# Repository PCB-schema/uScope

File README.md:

# uScope
Electron microscope
Project created with KiCAD v 5.0.2-bee76a0~70~ubuntu18.04.1, release build

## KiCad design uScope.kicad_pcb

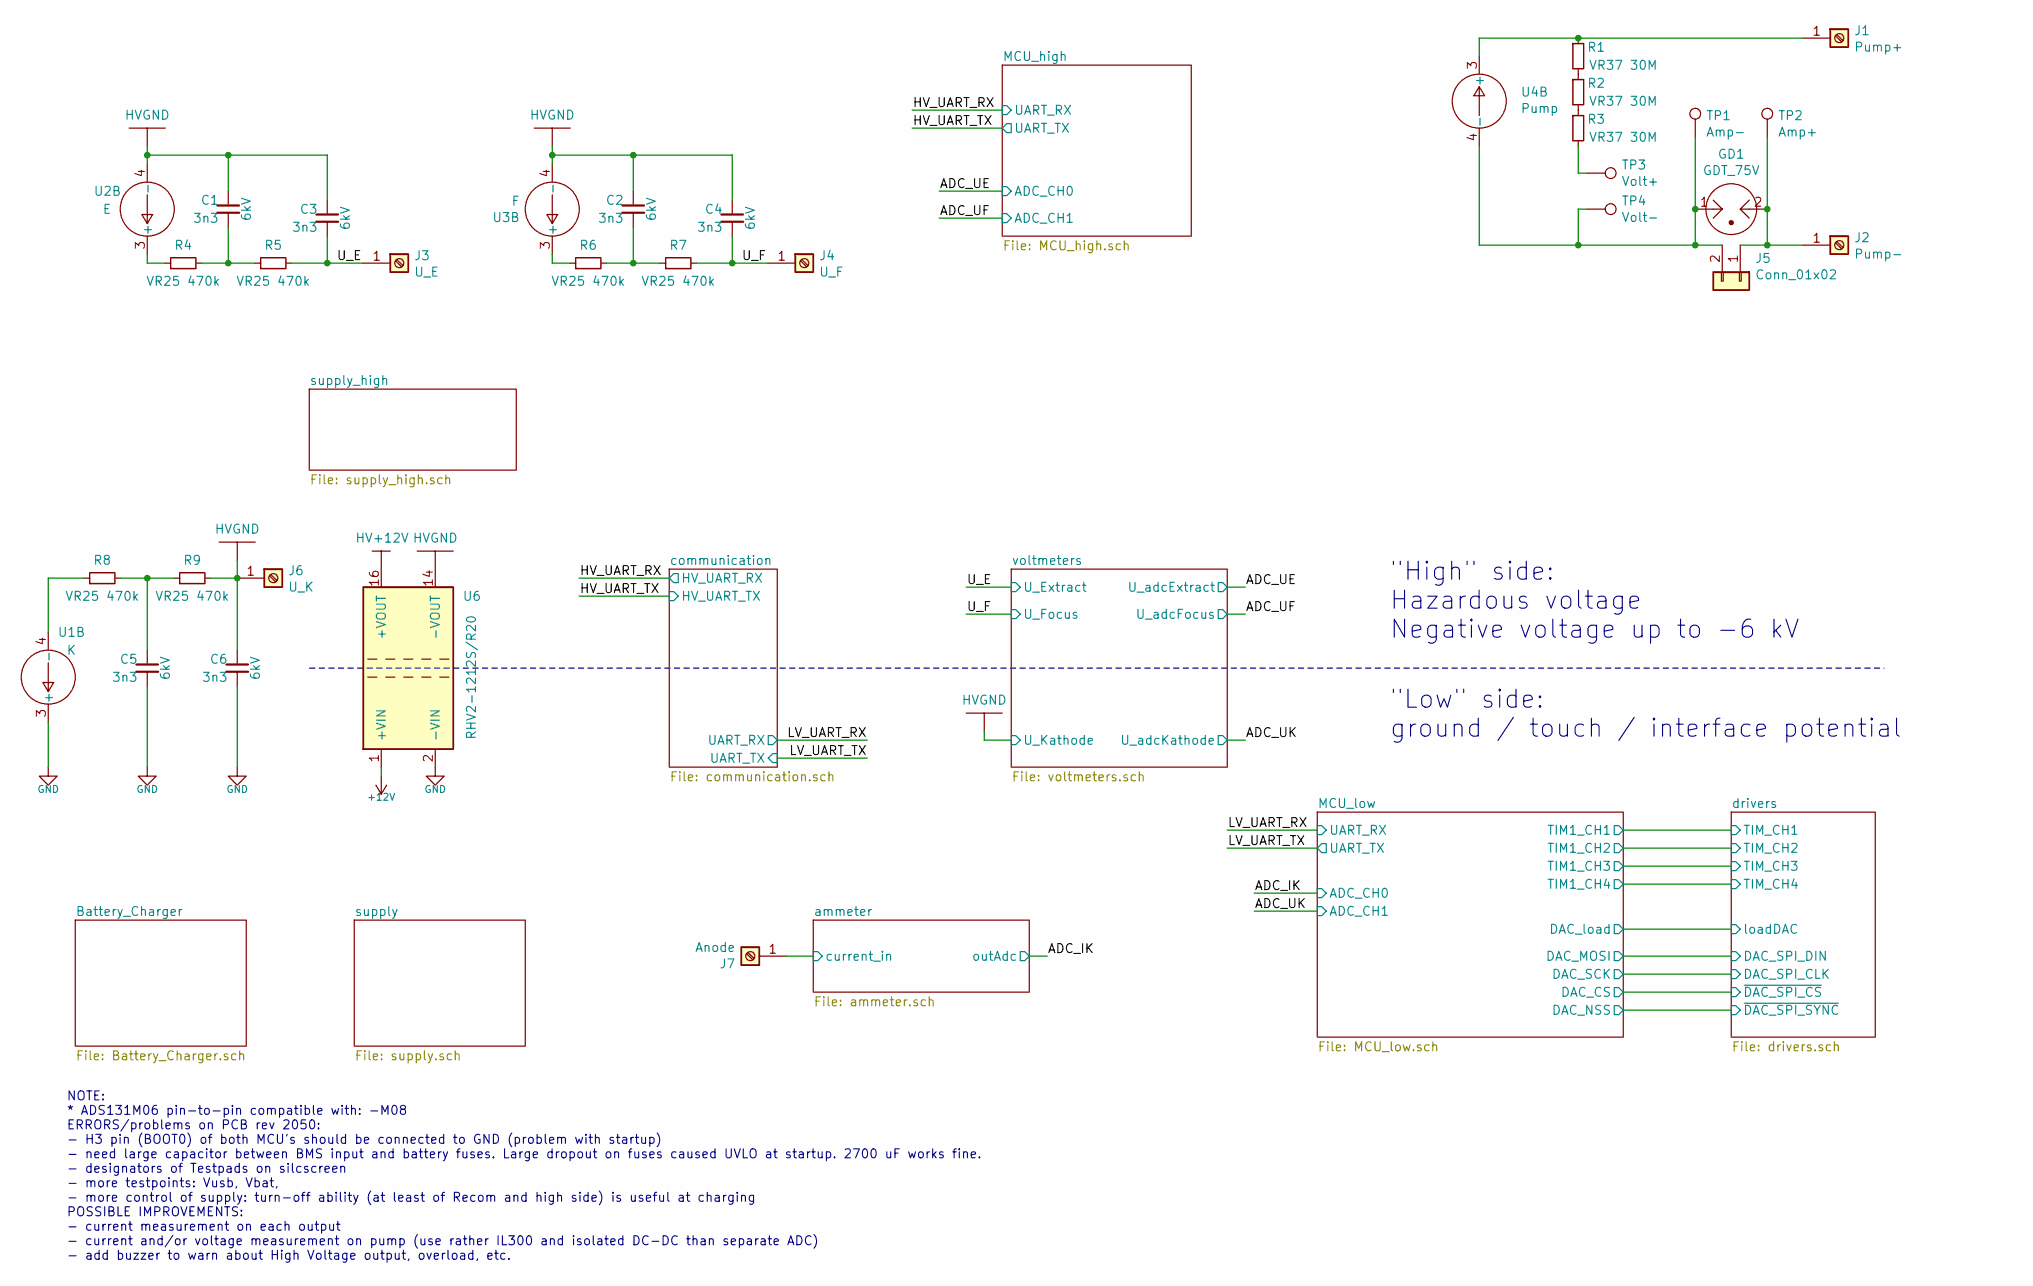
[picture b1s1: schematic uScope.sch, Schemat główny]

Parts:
C1, C2, C3, C4, C5, C6: 3n3; C_Rect_L26.5mm_W10.5mm_P22.50mm_MKS4; Voltage 6kV
GD1: GDT_75V; Arrester_Axial_L6mm_D6mm_P8.89mm_Horizontal
J1: Pump+; Terminal_Amp_HB0101
J2: Pump-; Terminal_Amp_HB0101
J3: U_E; Terminal_Amp_HB0101
J4: U_F; Terminal_Amp_HB0101
J5: Conn_01x02; PinHeader_1x02_P2.54mm_Vertical
J6: U_K; Terminal_Amp_HB0101
J7: Anode; Terminal_Amp_HB0101
R1, R2, R3: VR37 30M; R_Axial_DIN0411_L9.9mm_D3.6mm_P12.70mm_Horizontal
R4, R5, R6, R7, R8, R9: VR25 470k; R_Axial_DIN0207_L6.3mm_D2.5mm_P10.16mm_Horizontal
TP1: Amp-; Banana4mmSocket_black
TP2: Amp+; Banana4mmSocket_red
TP3: Volt+; Banana4mmSocket_red
TP4: Volt-; Banana4mmSocket_black
U1: K; DCDC_APD_P2_single
U2: E; DCDC_APD_P2_single
U3: F; DCDC_APD_P2_single
U4: Pump; DCDC_APD_P2_single
U6: RHV2-1212S/R20; SIP16_RECOM

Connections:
+12V: U6.1 (+VIN); also elsewhere on the board
/U_E: C3.2, J3.1, R5.2; also elsewhere on the board
/U_F: C4.2, J4.1, R7.2; also elsewhere on the board
/ammeter/current_in: J7.1; also elsewhere on the board
HV+12V: U6.16 (+VOUT); also elsewhere on the board
unnamed: C1.2, R4.2, R5.1
unnamed: C2.2, R6.2, R7.1
unnamed: C5.1, R8.2, R9.1
unnamed: GD1.1, J5.2, TP1.1, TP4.1, U4.4 (-)
unnamed: GD1.2, J2.1, J5.1, TP2.1
unnamed: J1.1, R1.1, U4.3 (+)
unnamed: R1.2, R2.1
unnamed: R2.2, R3.1
unnamed: R3.2, TP3.1
unnamed: R4.1, U2.3 (+)
unnamed: R6.1, U3.3 (+)
unnamed: R8.1, U1.4 (-)

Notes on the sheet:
NOTE: * ADS131M06 pin-to-pin compatible with: -M08 ERRORS/problems on PCB rev 2050: - H3 pin (BOOT0) of both MCU's should be connected to GND (problem with startup) - need large capacitor between BMS input and battery fuses. Large dropout on fuses caused UVLO at startup. 2700 uF works fine. - desig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
"High" side: Hazardous voltage Negative voltage up to -6 kV
"Low" side: ground / touch / interface potential

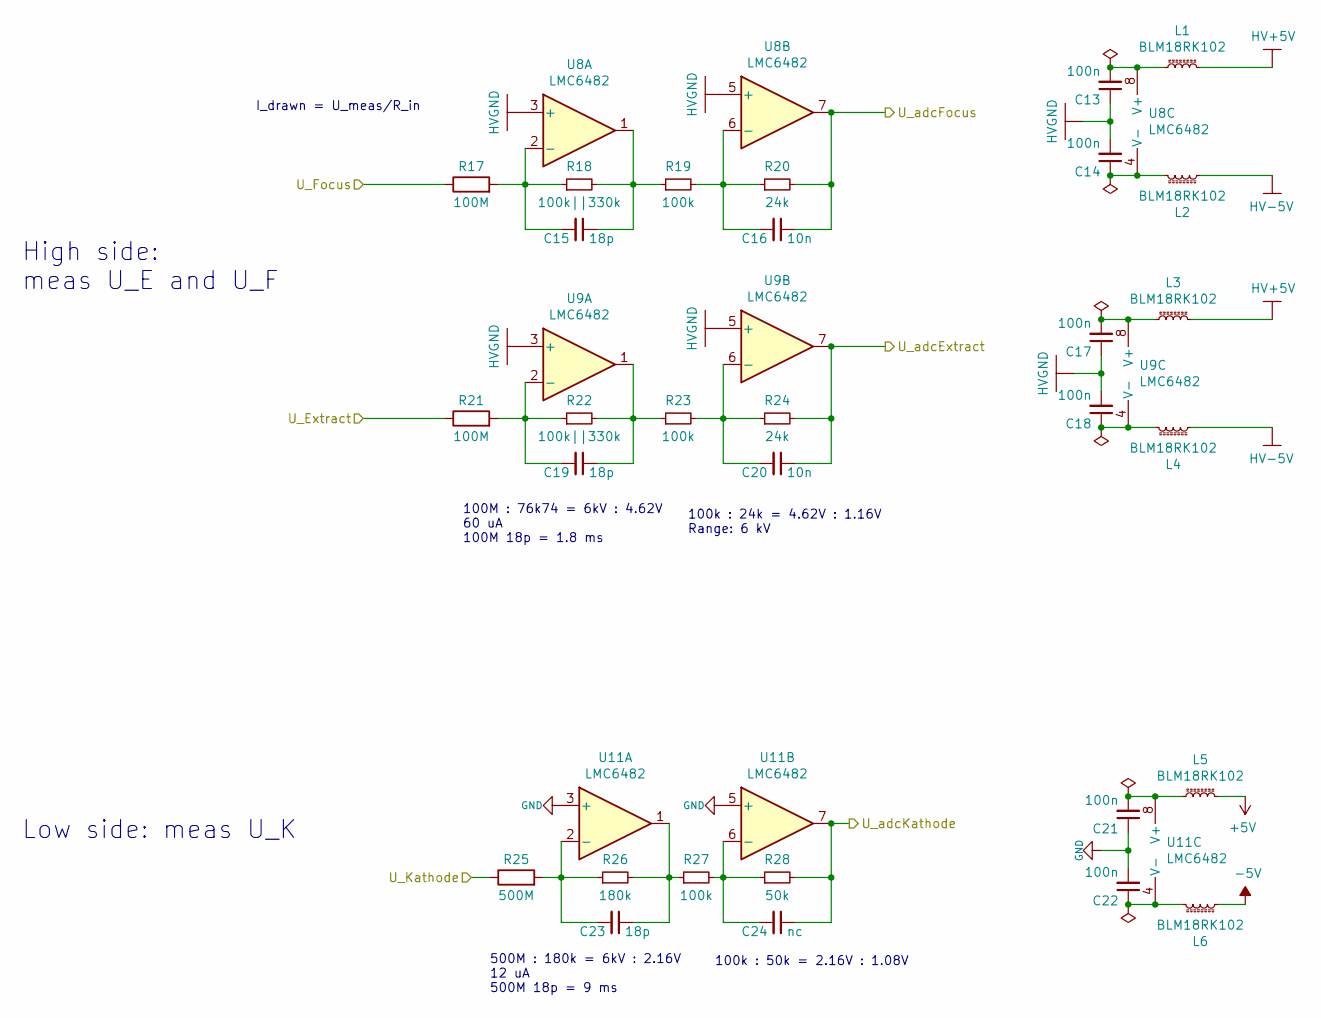
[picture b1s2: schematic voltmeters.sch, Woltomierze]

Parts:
C13, C14, C17, C18, C21, C22: 100n; C_0603_1608Metric
C15, C19, C23: 18p; C_0603_1608Metric
C16, C20: 10n; C_0603_1608Metric
C24: nc; C_0603_1608Metric
L1, L2, L3, L4, L5, L6: BLM18RK102; L_0603_1608Metric
R17, R21: 100M; MHR0317_0422_0424_0624SA
R18, R22: 100k||330k; R_0603_1608Metric
R19, R23, R27: 100k; R_0603_1608Metric
R20, R24: 24k; R_0603_1608Metric
R25: 500M; MHR0317_0422_0424_0624SA
R26: 180k; R_0603_1608Metric
R28: 50k; R_0603_1608Metric
U8, U9, U11: LMC6482; SO8-MSOP8_3x3mm_P0.65mm

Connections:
+5V: L5.2; also elsewhere on the board
-5V: L6.1; also elsewhere on the board
/ADC_UE: C20.1, R24.2, U9.7; also elsewhere on the board
/ADC_UF: C16.1, R20.2, U8.7; also elsewhere on the board
/ADC_UK: C24.1, R28.2, U11.7; also elsewhere on the board
/U_E: R21.1; also elsewhere on the board
/U_F: R17.1; also elsewhere on the board
HV+5V: L1.2, L3.2; also elsewhere on the board
HV-5V: L2.1, L4.1; also elsewhere on the board
unnamed: C13.2, L1.1, U8.8 (V+)
unnamed: C14.1, L2.2, U8.4 (V-)
unnamed: C15.1, R18.2, R19.1, U8.1
unnamed: C15.2, R17.2, R18.1, U8.2 (-)
unnamed: C16.2, R19.2, R20.1, U8.6 (-)
unnamed: C17.2, L3.1, U9.8 (V+)
unnamed: C18.1, L4.2, U9.4 (V-)
unnamed: C19.1, R22.2, R23.1, U9.1
unnamed: C19.2, R21.2, R22.1, U9.2 (-)
unnamed: C20.2, R23.2, R24.1, U9.6 (-)
unnamed: C21.2, L5.1, U11.8 (V+)
unnamed: C22.1, L6.2, U11.4 (V-)
unnamed: C23.1, R26.2, R27.1, U11.1
unnamed: C23.2, R25.2, R26.1, U11.2 (-)
unnamed: C24.2, R27.2, R28.1, U11.6 (-)

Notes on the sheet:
I_drawn = U_meas/R_in
Low side: meas U_K
High side: meas U_E and U_F
500M : 180k = 6kV : 2.16V 12 uA 500M 18p = 9 ms
100k : 50k = 2.16V : 1.08V
100M : 76k74 = 6kV : 4.62V 60 uA 100M 18p = 1.8 ms
100k : 24k = 4.62V : 1.16V Range: 6 kV

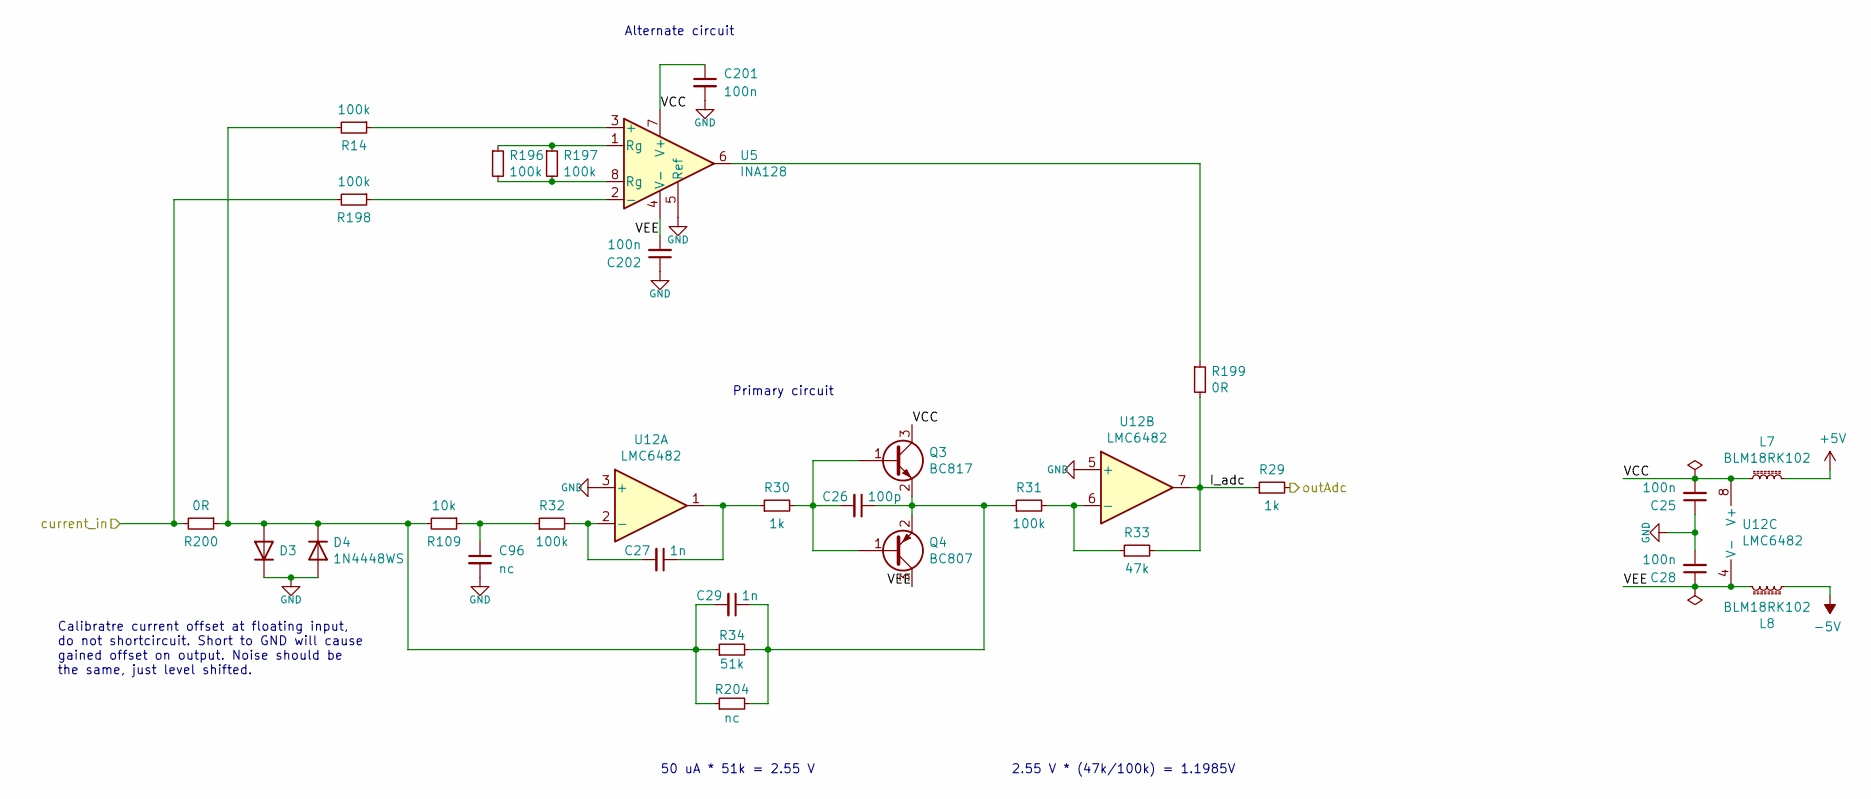
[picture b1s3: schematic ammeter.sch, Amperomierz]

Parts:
C25, C28, C201, C202: 100n; C_0603_1608Metric
C26: 100p; C_0603_1608Metric
C27: 1n; C_0603_1608Metric
C29: 1n; C_0603_1608Metric_Pad1.05x0.95mm_HandSolder
C96: nc; C_0603_1608Metric
D3, D4: 1N4448WS; D_SOD-323-523_HandSoldering
L7, L8: BLM18RK102; L_0603_1608Metric
Q3: BC817; SOT-23
Q4: BC807; SOT-23
R14, R31, R32, R198: 100k; R_0603_1608Metric
R29, R30: 1k; R_0603_1608Metric
R33: 47k; R_0603_1608Metric
R34: 51k; R_0603_1608Metric_Pad1.05x0.95mm_HandSolder
R109: 10k; R_0603_1608Metric
R196, R197: 100k; R_0603_1608Metric_Pad1.05x0.95mm_HandSolder
R199: 0R; R_0603_1608Metric
R200: 0R; R_0603_1608Metric_Pad1.05x0.95mm_HandSolder
R204: nc; R_1206_3216Metric
U5: INA128; SO-8_3.9x4.9mm_P1.27mm
U12: LMC6482; SO8-MSOP8_3x3mm_P0.65mm

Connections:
+5V: L7.2; also elsewhere on the board
-5V: L8.1; also elsewhere on the board
/ADC_IK: R29.2; also elsewhere on the board
/ammeter/I_adc: R29.1, R33.2, R199.2, U12.7
/ammeter/VCC: C25.2, C201.1, L7.1, Q3.3 (C), U5.7 (V+), U12.8 (V+)
/ammeter/VEE: C28.1, C202.2, L8.2, Q4.3 (C), U5.4 (V-), U12.4 (V-)
/ammeter/current_in: R198.2, R200.2; also elsewhere on the board
unnamed: C26.1, C29.1, Q3.2 (E), Q4.2 (E), R31.1, R34.2, R204.2
unnamed: C26.2, Q3.1 (B), Q4.1 (B), R30.2
unnamed: C27.1, R30.1, U12.1
unnamed: C27.2, R32.2, U12.2 (-)
unnamed: C29.2, D3.2 (A), D4.1 (K), R14.2, R34.1, R109.2, R200.1, R204.1
unnamed: C96.1, R32.1, R109.1
unnamed: R14.1, U5.3 (+)
unnamed: R31.2, R33.1, U12.6 (-)
unnamed: R196.1, R197.1, U5.1 (Rg)
unnamed: R196.2, R197.2, U5.8 (Rg)
unnamed: R198.1, U5.2 (-)
unnamed: R199.1, U5.6

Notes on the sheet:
Primary circuit
Alternate circuit
50 uA * 51k = 2.55 V
2.55 V * (47k/100k) = 1.1985V
Calibratre current offset at floating input, do not shortcircuit. Short to GND will cause gained offset on output. Noise should be the same, just level shifted.

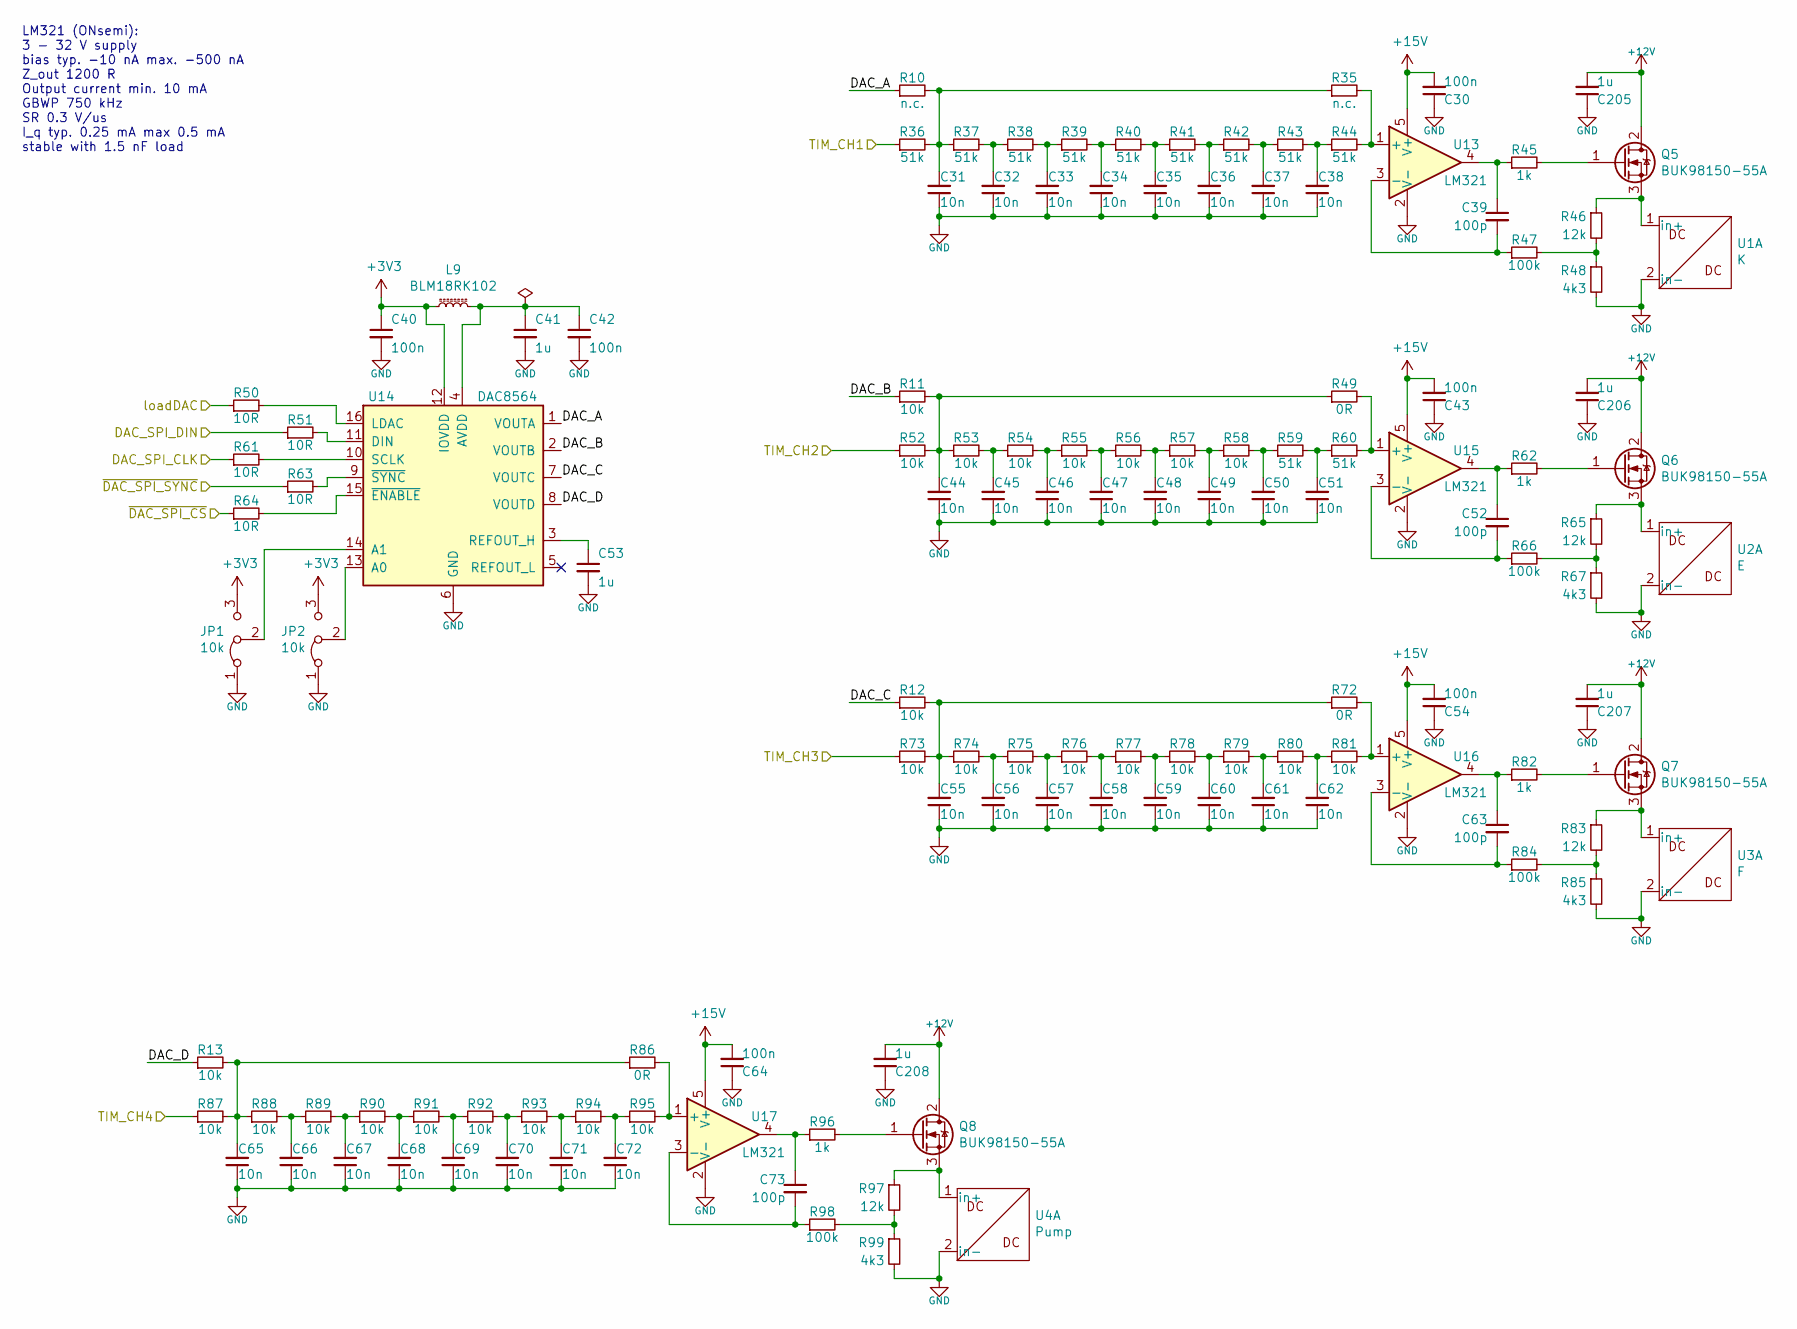
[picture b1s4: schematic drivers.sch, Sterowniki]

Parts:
C30, C40, C42, C43, C54, C64: 100n; C_0603_1608Metric
C31, C32, C33, C34, C35, C36, C37, C38, C44, C45, C46, C47, C48, C49, C50, C51, C55, C56, C57, C58, C59, C60, C61, C62, C65, C66, C67, C68, C69, C70, C71, C72: 10n; C_0603_1608Metric_Pad1.05x0.95mm_HandSolder
C39, C52, C63, C73: 100p; C_0603_1608Metric
C41, C53, C205, C206, C207, C208: 1u; C_0603_1608Metric
JP1, JP2: 10k; Jumper_3P_0603_1608Metric_open
L9: BLM18RK102; L_0603_1608Metric
Q5, Q6, Q7, Q8: BUK98150-55A; SOT-223-3_TabPin2
R10, R35: n.c.; R_0603_1608Metric_Pad1.05x0.95mm_HandSolder
R11, R12, R13, R52, R53, R54, R55, R56, R57, R58, R73, R74, R75, R76, R77, R78, R79, R80, R81, R87, R88, R89, R90, R91, R92, R93, R94, R95: 10k; R_0603_1608Metric_Pad1.05x0.95mm_HandSolder
R36, R37, R38, R39, R40, R41, R42, R43, R44, R59, R60: 51k; R_0603_1608Metric_Pad1.05x0.95mm_HandSolder
R45, R62, R82, R96: 1k; R_0603_1608Metric
R46, R65, R83, R97: 12k; R_0603_1608Metric_Pad1.05x0.95mm_HandSolder
R47, R66, R84, R98: 100k; R_0603_1608Metric
R48, R67, R85, R99: 4k3; R_0603_1608Metric_Pad1.05x0.95mm_HandSolder
R49, R72, R86: 0R; R_0603_1608Metric_Pad1.05x0.95mm_HandSolder
R50, R51, R61, R63, R64: 10R; R_0603_1608Metric
U1: K; DCDC_APD_P2_single
U2: E; DCDC_APD_P2_single
U3: F; DCDC_APD_P2_single
U4: Pump; DCDC_APD_P2_single
U13, U15, U16, U17: LM321; SOT-23-5
U14: DAC8564; TSSOP-16_4.4x5mm_P0.65mm

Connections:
+3V3: C40.1, JP1.3 (B), JP2.3 (B), L9.1, U14.12 (IOVDD); also elsewhere on the board
+12V: C205.2, C206.2, C207.2, C208.2, Q5.2 (D), Q6.2 (D), Q7.2 (D), Q8.2 (D); also elsewhere on the board
+15V: C30.2, C43.2, C54.2, C64.2, U13.5 (V+), U15.5 (V+), U16.5 (V+), U17.5 (V+); also elsewhere on the board
/MCU_low/DAC_CS: R64.1; also elsewhere on the board
/MCU_low/DAC_MOSI: R51.1; also elsewhere on the board
/MCU_low/DAC_NSS: R63.1; also elsewhere on the board
/MCU_low/DAC_SCK: R61.1; also elsewhere on the board
/MCU_low/DAC_load: R50.1; also elsewhere on the board
/MCU_low/TIM1_CH1: R36.1; also elsewhere on the board
/MCU_low/TIM1_CH2: R52.1; also elsewhere on the board
/MCU_low/TIM1_CH3: R73.1; also elsewhere on the board
/MCU_low/TIM1_CH4: R87.1; also elsewhere on the board
/drivers/DAC_A: R10.1, U14.1 (VOUTA)
/drivers/DAC_B: R11.1, U14.2 (VOUTB)
/drivers/DAC_C: R12.1, U14.7 (VOUTC)
/drivers/DAC_D: R13.1, U14.8 (VOUTD)
unnamed: C31.2, R10.2, R35.1, R36.2, R37.1
unnamed: C32.2, R37.2, R38.1
unnamed: C33.2, R38.2, R39.1
unnamed: C34.2, R39.2, R40.1
unnamed: C35.2, R40.2, R41.1
unnamed: C36.2, R41.2, R42.1
unnamed: C37.2, R42.2, R43.1
unnamed: C38.2, R43.2, R44.1
unnamed: C39.1, R45.1, U13.4
unnamed: C39.2, R47.1, U13.3 (-)
unnamed: C41.1, C42.1, L9.2, U14.4 (AVDD)
unnamed: C44.2, R11.2, R49.1, R52.2, R53.1
unnamed: C45.2, R53.2, R54.1
unnamed: C46.2, R54.2, R55.1
unnamed: C47.2, R55.2, R56.1
unnamed: C48.2, R56.2, R57.1
unnamed: C49.2, R57.2, R58.1
unnamed: C50.2, R58.2, R59.1
unnamed: C51.2, R59.2, R60.1
unnamed: C52.1, R62.1, U15.4
unnamed: C52.2, R66.1, U15.3 (-)
unnamed: C53.1, U14.3 (REFOUT_H)
unnamed: C55.2, R12.2, R72.1, R73.2, R74.1
unnamed: C56.2, R74.2, R75.1
unnamed: C57.2, R75.2, R76.1
unnamed: C58.2, R76.2, R77.1
unnamed: C59.2, R77.2, R78.1
unnamed: C60.2, R78.2, R79.1
unnamed: C61.2, R79.2, R80.1
unnamed: C62.2, R80.2, R81.1
unnamed: C63.1, R82.1, U16.4
unnamed: C63.2, R84.1, U16.3 (-)
unnamed: C65.2, R13.2, R86.1, R87.2, R88.1
unnamed: C66.2, R88.2, R89.1
unnamed: C67.2, R89.2, R90.1
unnamed: C68.2, R90.2, R91.1
unnamed: C69.2, R91.2, R92.1
unnamed: C70.2, R92.2, R93.1
unnamed: C71.2, R93.2, R94.1
unnamed: C72.2, R94.2, R95.1
unnamed: C73.1, R96.1, U17.4
unnamed: C73.2, R98.1, U17.3 (-)
unnamed: JP1.2 (C), U14.14 (A1)
unnamed: JP2.2 (C), U14.13 (A0)
unnamed: Q5.1 (G), R45.2
unnamed: Q5.3 (S), R46.1, U1.1 (in+)
unnamed: Q6.1 (G), R62.2
unnamed: Q6.3 (S), R65.1, U2.1 (in+)
unnamed: Q7.1 (G), R82.2
unnamed: Q7.3 (S), R83.1, U3.1 (in+)
unnamed: Q8.1 (G), R96.2
unnamed: Q8.3 (S), R97.1, U4.1 (in+)
unnamed: R35.2, R44.2, U13.1 (+)
unnamed: R46.2, R47.2, R48.1
unnamed: R49.2, R60.2, U15.1 (+)
unnamed: R50.2, U14.16 (LDAC)
unnamed: R51.2, U14.11 (DIN)
unnamed: R61.2, U14.10 (SCLK)
unnamed: R63.2, U14.9 (~SYNC)
unnamed: R64.2, U14.15 (~ENABLE)
unnamed: R65.2, R66.2, R67.1
unnamed: R72.2, R81.2, U16.1 (+)
unnamed: R83.2, R84.2, R85.1
unnamed: R86.2, R95.2, U17.1 (+)
unnamed: R97.2, R98.2, R99.1

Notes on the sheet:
LM321 (ONsemi): 3 - 32 V supply bias typ. -10 nA max. -500 nA Z_out 1200 R Output current min. 10 mA GBWP 750 kHz SR 0.3 V/us I_q typ. 0.25 mA max 0.5 mA stable with 1.5 nF load

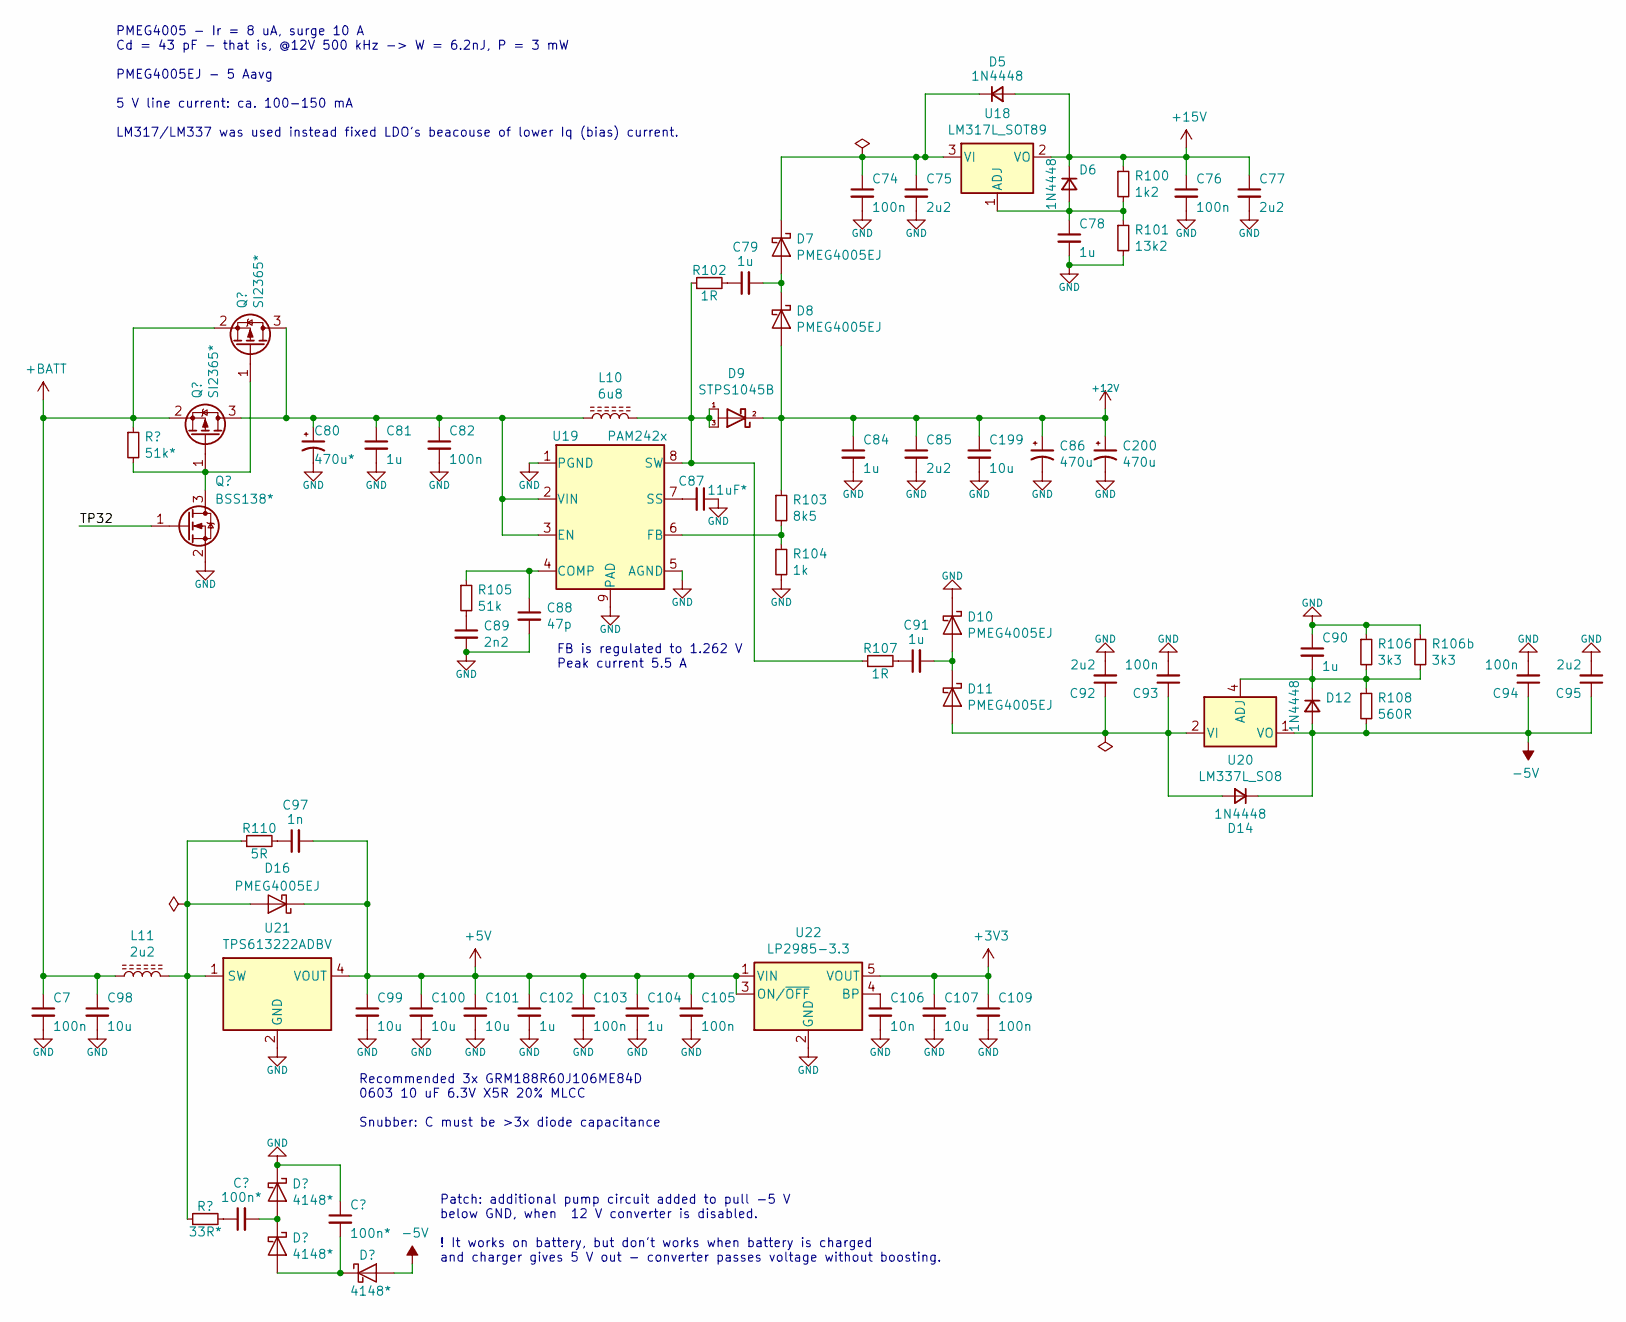
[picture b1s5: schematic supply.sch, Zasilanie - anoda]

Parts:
C7, C74, C76, C82, C93, C94, C103, C105, C109: 100n; C_0603_1608Metric
C75, C77, C85, C95: 2u2; C_0805_2012Metric
C78, C81, C84, C90, C91, C102, C104: 1u; C_0603_1608Metric
C79: 1u; C_0805_2012Metric_Pad1.15x1.40mm_HandSolder
C80: 470u*; CP_Radial_D6.3mm_P2.50mm
C86, C200: 470u; CP_Radial_D8.0mm_P3.50mm
C87: 11uF*; C_0603_1608Metric
C88: 47p; C_0603_1608Metric
C89: 2n2; C_0603_1608Metric
C92: 2u2; C_0805_2012Metric_Pad1.15x1.40mm_HandSolder
C97: 1n; C_0603_1608Metric
C98, C99, C100, C101, C107, C199: 10u; C_0603_1608Metric_Pad1.05x0.95mm_HandSolder
C106: 10n; C_0603_1608Metric
D5, D6, D12, D14: 1N4448; D_SOD-323-523_HandSoldering
D7, D8, D10, D11: PMEG4005EJ; D_SOD-323-523_HandSoldering
D9: STPS1045B; TO-252-2
D16: PMEG4005EJ; D_SOD-323-523-SMA_Universal_Handsoldering
L10: 6u8; L_Abracon_ASPI-0630LR
L11: 2u2; L_1008_2520Metric
R100: 1k2; R_0603_1608Metric
R101: 13k2; R_0603_1608Metric
R102, R107: 1R; R_0603_1608Metric_Pad1.05x0.95mm_HandSolder
R103: 8k5; R_0603_1608Metric
R104: 1k; R_0603_1608Metric
R105: 51k; R_0603_1608Metric
R106: 3k3; R_0603_1608Metric
R106b: 3k3
R108: 560R; R_0603_1608Metric
R110: 5R; R_0603_1608Metric_Pad1.05x0.95mm_HandSolder
U18: LM317L_SOT89; SOT-89-3
U19: PAM242x; SOIC-8-1EP_3.9x4.9mm_P1.27mm_EP2.41x3.3mm_ThermalVias
U20: LM337L_SO8; SOIC-8_3.9x4.9mm_P1.27mm
U21: TPS613222ADBV; SOT-23-5
U22: LP2985-3.3; SOT-23-5

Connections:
+3V3: C107.1, C109.1, U22.5 (VOUT); also elsewhere on the board
+5V: C97.2, C99.1, C100.1, C101.1, C102.1, C103.1, C104.1, C105.1, D16.1 (K), U21.4 (VOUT), U22.1 (VIN), U22.3 (ON/~OFF~); also elsewhere on the board
+12V: C84.1, C85.1, C86.1, C199.1, C200.1, D8.2 (A), D9.2 (K), R103.1; also elsewhere on the board
+15V: C76.1, C77.1, D5.2 (A), D6.1 (K), R100.1, U18.2 (VO); also elsewhere on the board
-5V: C94.1, C95.1, D12.2 (A), D14.1 (K), R108.2, U20.1 (VO); also elsewhere on the board
unnamed: C74.1, C75.1, D5.1 (K), D7.1 (K), U18.3 (VI)
unnamed: C78.1, D6.2 (A), R100.2, R101.1, U18.1 (ADJ)
unnamed: C79.1, R102.2
unnamed: C79.2, D7.2 (A), D8.1 (K)
unnamed: C87.2, U19.7 (SS)
unnamed: C88.1, R105.1, U19.4 (COMP)
unnamed: C89.1, R105.2
unnamed: C90.2, D12.1 (K), R106.2, R106b.2, R108.1, U20.4 (ADJ)
unnamed: C91.1, R107.2
unnamed: C91.2, D10.2 (A), D11.1 (K)
unnamed: C92.1, C93.1, D11.2 (A), D14.2 (A), U20.2 (VI), U20.3 (VI), U20.6 (VI), U20.7 (VI)
unnamed: C97.1, R110.2
unnamed: C106.1, U22.4 (BP)
unnamed: D9.1 (A), D9.3 (A), L10.2, R102.1, R107.1, U19.8 (SW)
unnamed: D16.2 (A), L11.2, R110.1, U21.1 (SW)
unnamed: R103.2, R104.1, U19.6 (FB)

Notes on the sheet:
FB is regulated to 1.262 V Peak current 5.5 A
PMEG4005 - Ir = 8 uA, surge 10 A Cd = 43 pF - that is, @12V 500 kHz -> W = 6.2nJ, P = 3 mW PMEG4005EJ - 5 Aavg 5 V line current: ca. 100-150 mA LM317/LM337 was used instead fixed LDO's beacouse of lower Iq (bias) current.
Recommended 3x GRM188R60J106ME84D 0603 10 uF 6.3V X5R 20% MLCC Snubber: C must be >3x diode capacitance
Patch: additional pump circuit added to pull -5 V below GND, when 12 V converter is disabled. ! It works on battery, but don't works when battery is charged and charger gives 5 V out - converter passes voltage without boosting.

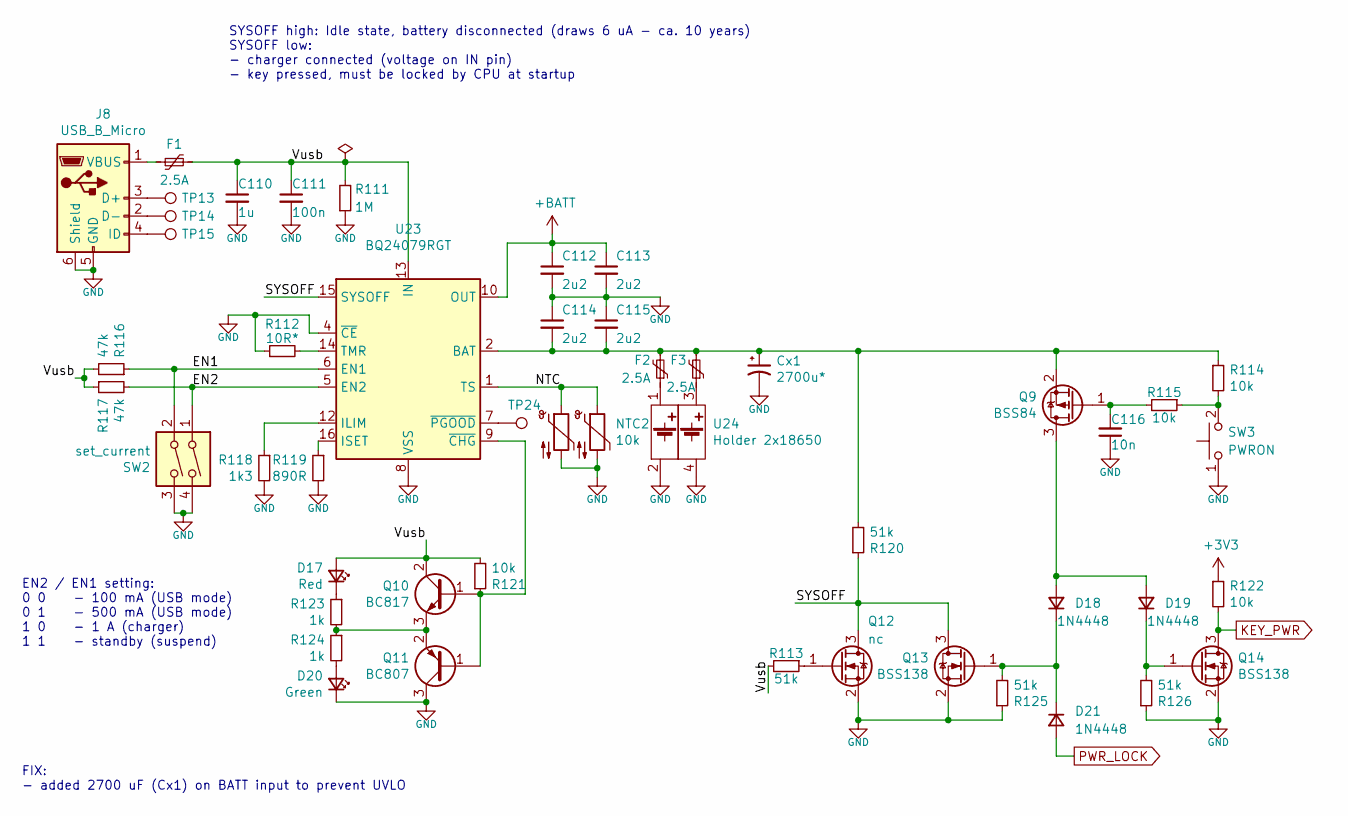
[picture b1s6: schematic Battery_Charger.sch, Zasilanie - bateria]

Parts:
C110: 1u; C_0603_1608Metric
C111: 100n; C_0603_1608Metric
C112, C113, C114, C115: 2u2; C_0805_2012Metric
C116: 10n; C_0603_1608Metric
Cx1: 2700u*
D17: Red; D_0805_2012Metric_Pad1.15x1.40mm_HandSolder
D18, D19, D21: 1N4448; D_SOD-323-523_HandSoldering
D20: Green; D_0805_2012Metric_Pad1.15x1.40mm_HandSolder
F1, F2, F3: 2.5A; Fuse_1812_4532Metric_Pad1.30x3.40mm_HandSolder
J8: USB_B_Micro; USB_Micro-B_Amphenol_10118194_Horizontal
NTC1: 10k; R_1206_3216Metric_Pad1.42x1.75mm_HandSolder
NTC2: 10k; R_Axial_DIN0204_L3.6mm_D1.6mm_P2.54mm_Vertical
Q9: BSS84; SOT-23
Q10: BC817; SOT-23
Q11: BC807; SOT-23
Q12: nc; SOT-23
Q13, Q14: BSS138; SOT-23
R111: 1M; R_0603_1608Metric
R112: 10R*; R_0603_1608Metric
R113, R120, R125, R126: 51k; R_0603_1608Metric
R114, R115, R121, R122: 10k; R_0603_1608Metric
R116, R117: 47k; R_0603_1608Metric
R118: 1k3; R_0603_1608Metric_Pad1.05x0.95mm_HandSolder
R119: 890R; R_0603_1608Metric_Pad1.05x0.95mm_HandSolder
R123, R124: 1k; R_0603_1608Metric
SW2: set_current; SW_DIP_SPSTx02_Slide_6.7x6.64mm_W8.61mm_P2.54mm_LowProfile
SW3: PWRON; SW_Push_1P1T_NO_6x6mm_H9.5mm
TP13, TP14, TP15, TP24: TestPoint; TestPoint_THTPad_D1.5mm_Drill0.7mm
U23: BQ24079RGT; VQFN-16-1EP_3x3mm_P0.5mm_EP1.6x1.6mm
U24: Holder 2x18650; BatteryHolder_Eagle-12BHC186P

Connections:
+3V3: R122.1; also elsewhere on the board
/Battery_Charger/EN1: R116.1, SW2.2, U23.6 (EN1)
/Battery_Charger/EN2: R117.2, SW2.1, U23.5 (EN2)
/Battery_Charger/NTC: NTC1.1, NTC2.1, U23.1 (TS)
/Battery_Charger/SYSOFF: Q12.3 (D), Q13.3 (D), R120.1, U23.15 (SYSOFF)
/Battery_Charger/Vusb: C110.1, C111.1, D17.2 (A), F1.2, Q10.2 (C), R111.2, R113.2, R116.2, R117.1, R121.2, U23.13 (IN)
KEY_PWR: Q14.3 (D), R122.2; also elsewhere on the board
unnamed: C114.2, C115.2, Cx1.1, F2.2, F3.2, Q9.2 (S), R114.1, R120.2, U23.2 (BAT), U23.3 (BAT)
unnamed: C116.2, Q9.1 (G), R115.2
unnamed: D17.1 (K), R123.1
unnamed: D18.1 (K), D21.1 (K), Q13.1 (G), R125.2
unnamed: D18.2 (A), D19.2 (A), Q9.3 (D)
unnamed: D19.1 (K), Q14.1 (G), R126.2
unnamed: D20.2 (A), R124.2
unnamed: F1.1, J8.1 (VBUS)
unnamed: F2.1, U24.1 (1+)
unnamed: F3.1, U24.3 (2+)
unnamed: J8.2 (D-), TP14.1
unnamed: J8.3 (D+), TP13.1
unnamed: J8.4 (ID), TP15.1
unnamed: Q10.1 (B), Q11.1 (B), R121.1, U23.9 (~CHG)
unnamed: Q10.3 (E), Q11.2 (E), R123.2, R124.1
unnamed: Q12.1 (G), R113.1
unnamed: R112.2, U23.14 (TMR)
unnamed: R114.2, R115.1, SW3.2
unnamed: R118.1, U23.12 (ILIM)
unnamed: R119.1, U23.16 (ISET)
unnamed: TP24.1, U23.7 (~PGOOD)
PWR_LOCK: D21.2 (A); also elsewhere on the board

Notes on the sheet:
SYSOFF high: Idle state, battery disconnected (draws 6 uA - ca. 10 years) SYSOFF low: - charger connected (voltage on IN pin) - key pressed, must be locked by CPU at startup
EN2 / EN1 setting: 0 0 - 100 mA (USB mode) 0 1 - 500 mA (USB mode) 1 0 - 1 A (charger) 1 1 - standby (suspend)
FIX: - added 2700 uF (Cx1) on BATT input to prevent UVLO
